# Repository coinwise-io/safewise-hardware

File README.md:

# safewise-hardware

SafeWISE hardware design including shematic, board, position files, gerber files etc. The hardware design was made using KiCad.

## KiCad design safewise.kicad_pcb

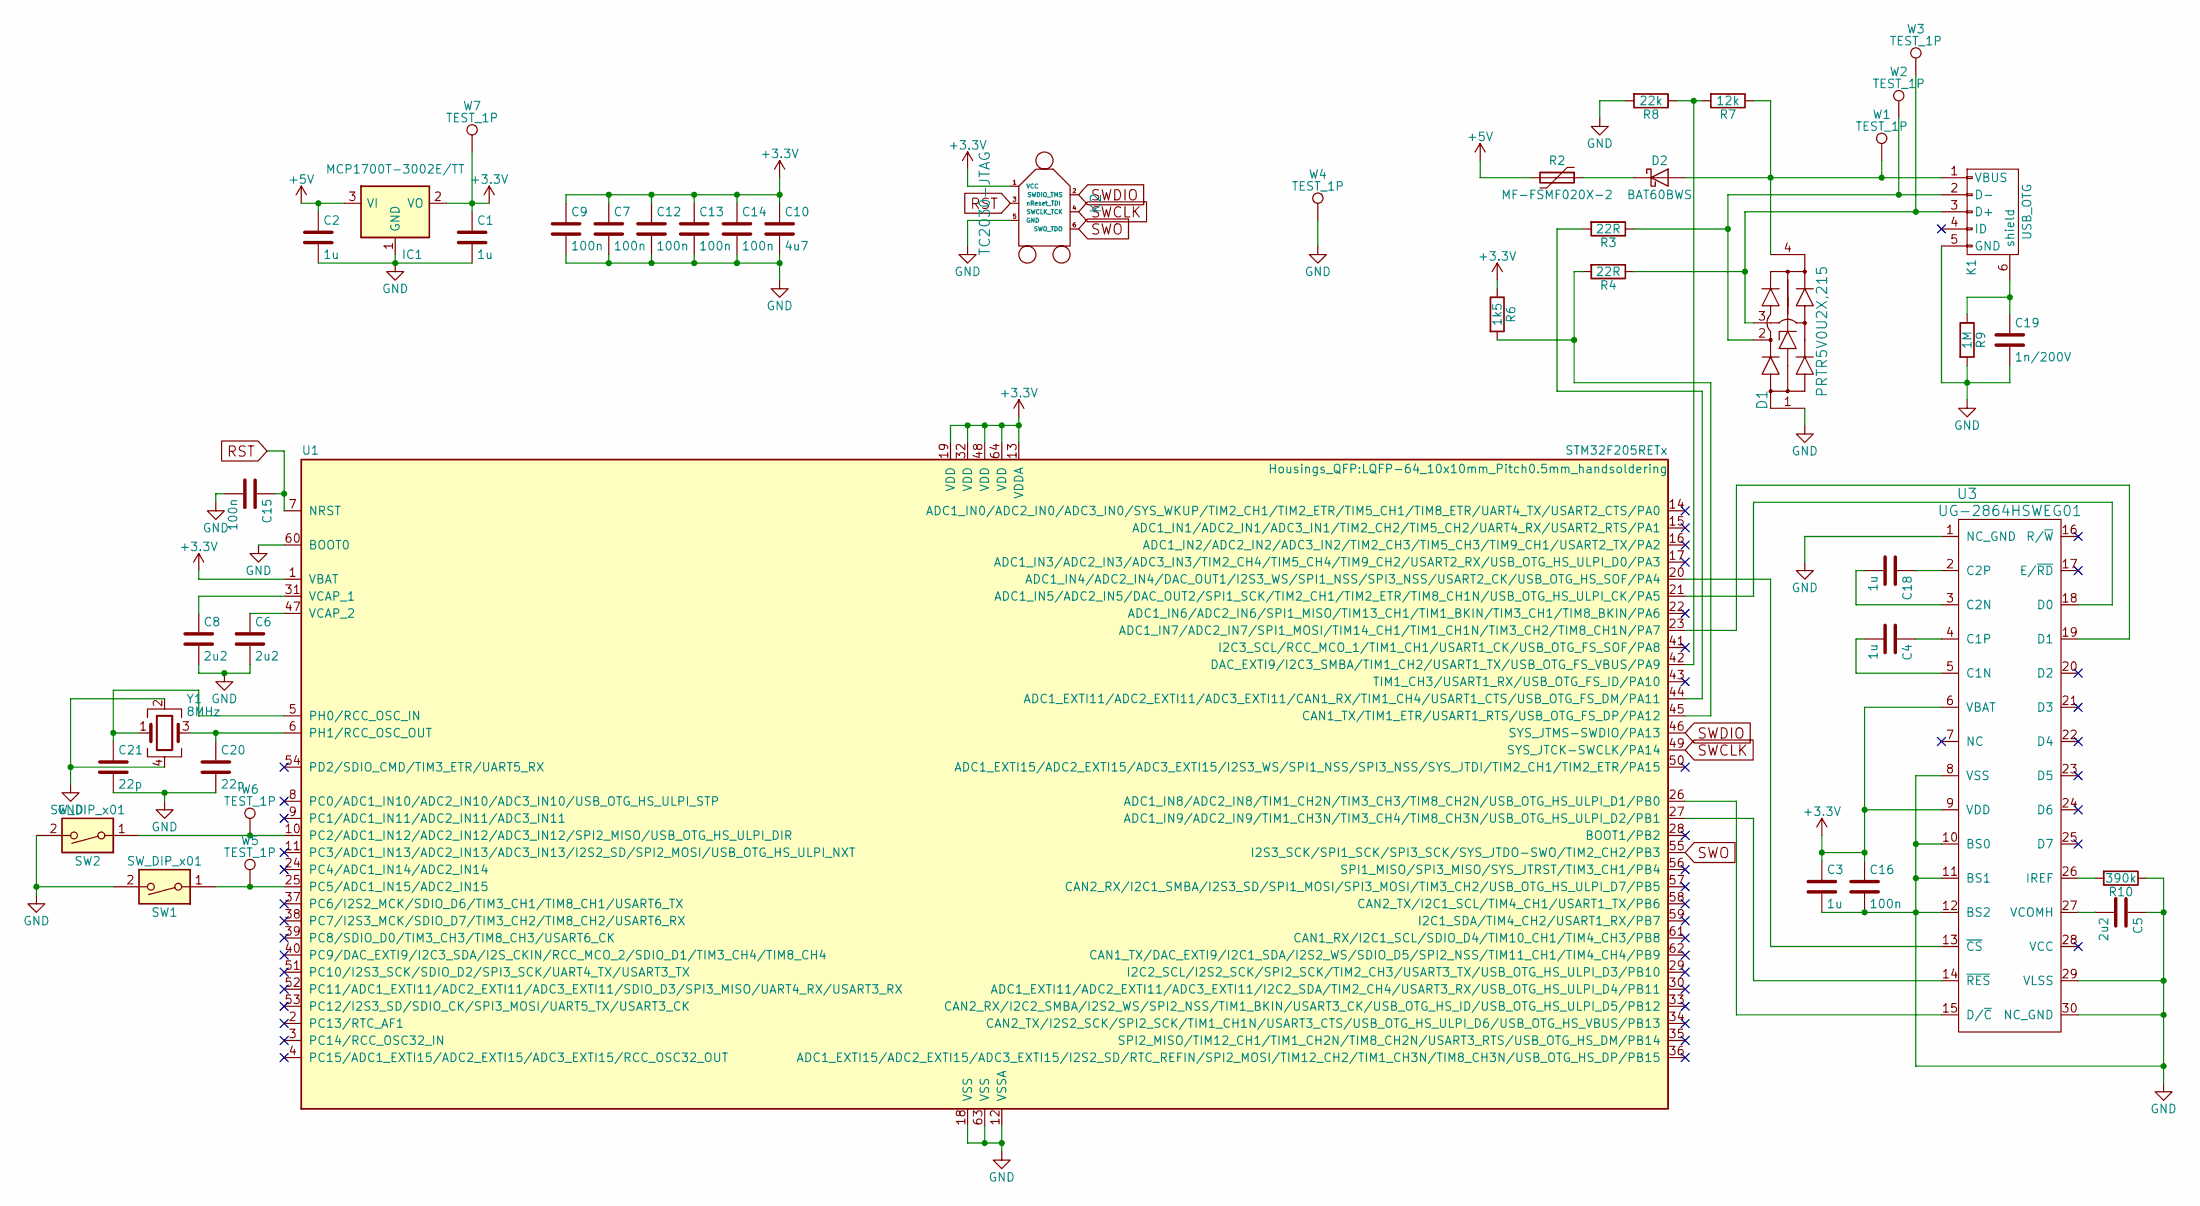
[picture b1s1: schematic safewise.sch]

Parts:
C1, C2, C3, C4, C18: 1u; C_0603_HandSoldering
C5, C6, C8: 2u2; C_0603_HandSoldering
C7, C9, C12, C13, C14, C15, C16: 100n; C_0603_HandSoldering
C10: 4u7; C_0603_HandSoldering
C19: 1n/200V; C_0603_HandSoldering
C20, C21: 22p; C_0603_HandSoldering
D1: PRTR5V0U2X,215; SOT-143_Handsoldering
D2: BAT60BWS; SOD-323_HandSoldering
IC1: MCP1700T-3002E/TT; SOT-23_Handsoldering
K1: USB_OTG; USB_Micro_B-10118194-0001LF_handsoldering
K2: TC2030-JTAG; Pin_Header_Straight_1x06
R2: MF-FSMF020X-2; R_0603_HandSoldering
R3, R4: 22R; R_0603_HandSoldering
R6: 1k5; R_0603_HandSoldering
R7: 12k; R_0603_HandSoldering
R8: 22k; R_0603_HandSoldering
R9: 1M; R_0603_HandSoldering
R10: 390k; R_0603_HandSoldering
SW1, SW2: SW_DIP_x01; SW_SPST_SKQG_handsoldering
U1: STM32F205RETx; LQFP-64_10x10mm_Pitch0.5mm_handsoldering
U3: UG-2864HSWEG01; UG-2864HSWEG01_handsoldering
W1, W2, W3, W4, W5, W6, W7: TEST_1P; Measurement_Point_Round-SMD-Pad_Small
Y1: 8MHz; Crystal_SMD_0603-4pin_6.0x3.5mm_HandSoldering

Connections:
+3V3: C1.1, C3.1, C7.1, C9.1, C10.1, C12.1, C13.1, C14.1, C16.1, IC1.2 (VO), K2.1 (VCC), R6.1, U1.1 (VBAT), U1.13 (VDDA), U1.19 (VDD), U1.32 (VDD), U1.48 (VDD), U1.64 (VDD), U3.6 (VBAT), U3.9 (VDD), W7.1
+5V: C2.1, IC1.3 (VI), R2.2
GND: C1.2, C2.2, C3.2, C5.1, C6.2, C7.2, C8.2, C9.2, C10.2, C12.2, C13.2, C14.2, C15.2, C16.2, C19.2, C20.2, C21.2, D1.1, IC1.1 (GND), K1.5 (GND), K2.5 (GND), R8.2, R9.2, R10.1, SW1.2, SW2.2, U1.12 (VSSA), U1.18 (VSS), U1.60 (BOOT0), U1.63 (VSS), U3.1 (NC_GND), U3.8 (VSS), U3.10 (BS0), U3.11 (BS1), U3.12 (BS2), U3.29 (VLSS), U3.30 (NC_GND), W4.1, Y1.2, Y1.4
unnamed: C4.1, U3.4 (C1P)
unnamed: C4.2, U3.5 (C1N)
unnamed: C5.2, U3.27 (VCOMH)
unnamed: C6.1, U1.47 (VCAP_2)
unnamed: C8.1, U1.31 (VCAP_1)
unnamed: C18.1, U3.2 (C2P)
unnamed: C18.2, U3.3 (C2N)
unnamed: C19.1, K1.6 (shield), R9.1
unnamed: C20.1, U1.6 (PH1/RCC_OSC_OUT), Y1.3
unnamed: C21.1, U1.5 (PH0/RCC_OSC_IN), Y1.1
unnamed: D1.2, K1.2 (D-), R3.1, W2.1
unnamed: D1.3, K1.3 (D+), R4.1, W3.1
unnamed: D1.4, D2.2 (A), K1.1 (VBUS), R7.1, W1.1
unnamed: D2.1 (K), R2.1
unnamed: R3.2, U1.44 (ADC1_EXTI11/ADC2_EXTI11/ADC3_EXTI11/CAN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)
unnamed: R4.2, R6.2, U1.45 (CAN1_TX/TIM1_ETR/USART1_RTS/USB_OTG_FS_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)
unnamed: R7.2, R8.1, U1.42 (DAC_EXTI9/I2C3_SMBA/TIM1_CH2/USART1_TX/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)
unnamed: R10.2, U3.26 (IREF)
unnamed: SW1.1, U1.25 (PC5/ADC1_IN15/ADC2_IN15), W5.1
unnamed: SW2.1, U1.10 (PC2/ADC1_IN12/ADC2_IN12/ADC3_IN12/SPI2_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), W6.1
unnamed: U1.20 (ADC1_IN4/ADC2_IN4/DAC_OUT1/I2S3_WS/SPI1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), U3.13 (~CS)
unnamed: U1.21 (ADC1_IN5/ADC2_IN5/DAC_OUT2/SPI1_SCK/TIM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), U3.18 (D0)
unnamed: U1.23 (ADC1_IN7/ADC2_IN7/SPI1_MOSI/TIM14_CH1/T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), U3.19 (D1)
unnamed: U1.26 (ADC1_IN8/ADC2_IN8/TIM1_CH2N/TIM3_CH3/TI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), U3.15 (D/~C)
unnamed: U1.27 (ADC1_IN9/ADC2_IN9/TIM1_CH3N/TIM3_CH4/TI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), U3.14 (~RES)
RST: C15.1, K2.3 (nReset_TDI), U1.7 (NRST)
SWCLK: K2.4 (SWCLK_TCK), U1.49 (SYS_JTCK-SWCLK/PA14)
SWDIO: K2.2 (SWDIO_TMS), U1.46 (SYS_JTMS-SWDIO/PA13)
SWO: K2.6 (SWO_TDO), U1.55 (I2S3_SCK/SPI1_SCK/SPI3_SCK/SYS_JTDO-SWO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)

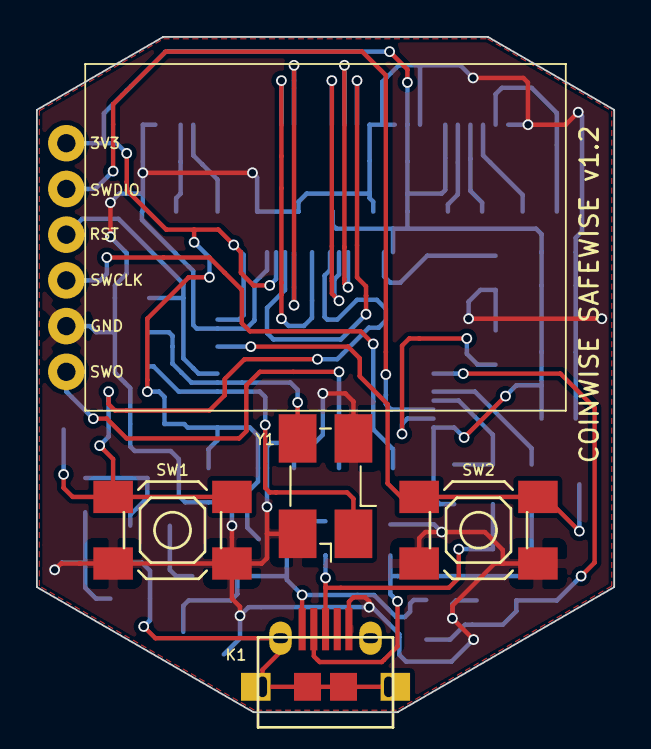
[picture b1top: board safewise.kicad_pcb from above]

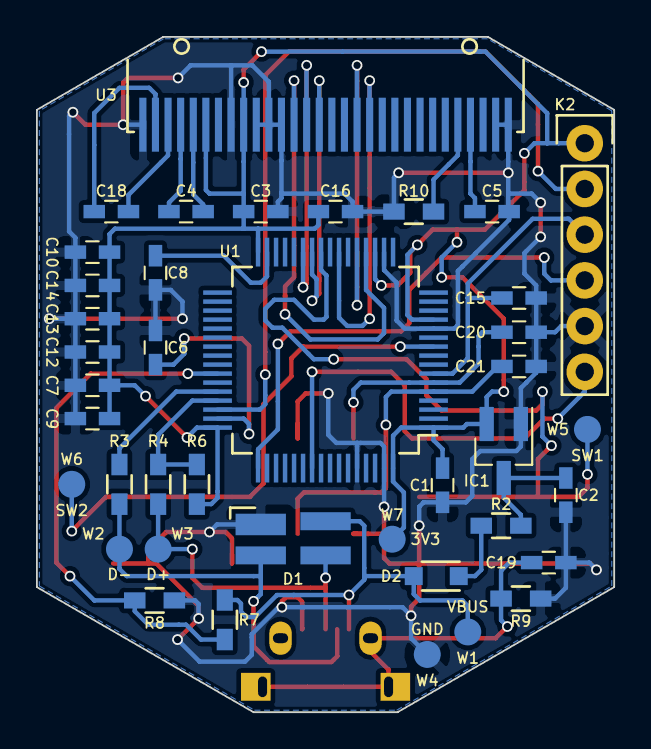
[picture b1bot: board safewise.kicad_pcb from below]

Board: 2 copper layers, 32.1 x 37.5 mm, 44 parts (40 on the bottom side), 32 nets.

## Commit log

2018-09-18 SafeWISE pcb version 1.0
2018-09-18 SafeWISE pcb version 1.1
2018-09-18 SafeWISE pcb version 1.2
2018-09-18 Create LICENSE
